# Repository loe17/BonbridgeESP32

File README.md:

# BonbridgeESP32

**Mach deinen USB-Bondrucker zum Netzwerk- und WLAN-Drucker für dein Kassensystem.**

Viele Kassensysteme (wie z. B. Kassensoftware, Gastronomiesoftware oder Kassen-Apps) können Bondrucker nur über das Netzwerk über eine **IP-Adresse und Port 9100** ansprechen. USB-Drucker können sie oft nicht direkt verwenden.

**BonbridgeESP32** löst dieses Problem mit einem kleinen, sparsamen Mikrocontroller (ESP32-S3):
Er nimmt Druckaufträge über ein **Netzwerkkabel (LAN)** oder über **WLAN** entgegen und leitet sie ohne Verzögerung direkt an deinen USB-Bondrucker weiter.

---

## Funktionen im Überblick

* **LAN & WLAN mit automatischer Umschaltung:**
  * **Kabel hat Vorrang:** Sobald ein Netzwerkkabel eingesteckt ist, nutzt der Adapter ausschließlich das Kabel. Das WLAN-Funkmodul wird komplett ausgeschaltet (spart Strom und schont das Funknetz).
  * **WLAN als Reserve:** Wird das Kabel abgezogen oder ist keins gesteckt, schaltet der Adapter automatisch das WLAN ein und verbindet sich mit deinem hinterlegten Funknetz.
* **Port 9100 RAW-Drucker-Server:** Der weltweite Standard für Netzwerk-Bondrucker. Druckdaten werden 1:1 an den USB-Drucker gestreamt.
* **1 Drucker pro Adapter:** Maximale Zuverlässigkeit – keine Vermischung von Bons.
* **Extrem sparsame Einstellungsseite (Web-Oberfläche):**
  * Im Browser erreichbar über die IP-Adresse des Geräts (`http://<ip>/`).
  * Verbraucht im Hintergrund **0 % Rechenleistung**, wenn sie nicht aufgerufen wird.
  * Zeigt sofort an, **worüber aktuell kommuniziert wird** (🟢 *LAN-Kabel aktiv* oder 🔵 *WLAN aktiv*).
  * Test-Knöpfe für **Drucktest** und **Kassenlade öffnen**.
  * Auswahl des **Druckprofils** (Epson TM-T88, Standard 80 mm, Kompakt 58 mm, Star).
  * Schalter: **Hinweis drucken wenn Netzwerk ausfällt**.
* **Bequeme WLAN-Suche & Live-Verbindung in der Web-Oberfläche:**
  * **🔍 WLAN suchen:** Findet alle Funknetze in Reichweite mit Signalstärke (z. B. 📶 85%) und Schlosssymbol. Ein Klick genügt, um das gewünschte WLAN auszuwählen.
  * **Passwort einblenden (👁️):** Zeigt das eingegebene Passwort im Klartext an, um Tippfehler sofort zu vermeiden.
  * **Direkt verbinden mit Live-Rückmeldung:** Ein Klick auf *„Mit diesem WLAN verbinden“* stellt die Verbindung her und zeigt nach wenigen Sekunden die neue IP-Adresse als anklickbaren Link an – oder bei Fehlern (z. B. Passwort falsch) eine verständliche Erklärung.
  * **Automatischer Einrichtungs-Hotspot (`Bonbridge-Setup`):** Ist noch kein WLAN hinterlegt oder der Router nicht erreichbar, spannt der Adapter ein eigenes Hilfsnetzwerk auf (`Bonbridge-Setup` unter `http://192.168.4.1`). So kann man das WLAN kinderleicht direkt vom Smartphone oder Laptop einrichten!
* **Drahtlose Firmware-Aktualisierung (Funk-Update / OTA) mit Versionsprüfung:**
  * **🔍 Automatische Versionsprüfung:** Ein Klick auf *„Nach Versionen auf GitHub suchen“* prüft, ob eine neuere Version bereitsteht oder man bereits aktuell ist.
  * **Auswahlmenü für Updates & Downgrades:** Zeigt alle jemals veröffentlichten Versionen an. Man kann mit einem Klick auf eine neuere Version aktualisieren oder bei Bedarf auf eine ältere Version zurückspringen (Downgrade).
  * **Manuelle Datei:** Ermöglicht das Hochladen einer eigenen `.bin`-Datei direkt über den Web-Browser.
  * **Live-Balken & Sicherheit:** Zeigt den Fortschritt von 0–100 % in Echtzeit an; alle gespeicherten WLAN- und Druckereinstellungen bleiben beim Update vollständig erhalten.
* **Netzwerk-Wächter (Ausfall-Alarm):**
  * Bricht die Netzwerkverbindung komplett ab, druckt der Drucker selbstständig einen Warnzettel aus:  
    *„Achtung: Netzwerkverbindung unterbrochen! Bitte LAN-Kabel oder Router prüfen.“*

---

## Benötigte Hardware

1. **Mikrocontroller:** **ESP32-S3** (z. B. ESP32-S3-DevKitC-1).  
   *(Wichtig: Ein älterer, klassischer ESP32 kann keine USB-Geräte als Host ansteuern – daher muss es ein ESP32-S3 sein!)*
2. **Netzwerk-Aufsatz:** **WIZnet W5500** SPI-Ethernet-Modul (für den LAN-Kabelanschluss).
3. **USB-OTG-Kabel / Buchse:** Zum Anstecken des Druckers an den ESP32-S3.
4. **Stromversorgung:** Über die Pins (5V und GND), z. B. von einem stabilen 5V-Netzteil oder dem 5V-Ausgang des Druckers.
5. **Bondrucker:** Beliebiger USB-ESC/POS-Bondrucker (z. B. Epson TM-T88V/VI, Munbyn, Bixolon, etc.).

---

## Verkabelung (Pin-Belegung)

### 1. Stromversorgung
| Netzteil / Quelle | ESP32-S3 Pin | Hinweise |
|---|---|---|
| **+5V (Plus)** | **5V** (bzw. VIN) | Stabiles 5V-Netzteil (mindestens **1,5 A bis 2 A** empfohlen) |
| **GND (Minus)** | **GND** | Gemeinsame Masse |

> [!TIP]
> **Tipps für eine stabile 5V-Stromversorgung:**
> * **5V über Pins oder USB:** Du kannst den ESP32-S3 über die Pins (**5V** und **GND**) mit einem 5V-Labornetzteil/Netzteil versorgen, oder direkt über ein 5V-USB-Netzteil (am besten mit Standard USB-A auf USB-C Kabel).
> * **Messpunkt zur Kontrolle:** Liegt an den Pins 5V an, muss am Pin **3V3** (gegen GND gemessen) eine saubere Spannung von 3,3 Volt anliegen.
> * Verwende möglichst **kurze und dicke Kabel** (keine langen, hauchdünnen Steckbrett-Drähte). Beim Senden von WLAN-Daten benötigt der Funkchip kurzzeitig Stromspitzen bis zu 450 mA – zu dünne Drähte führen zu einem Spannungsabfall (Brownout).
> * Das System verfügt über eine integrierte **Spannungsüberwachung**: Auf der Weboberfläche siehst du in der Zeile *„System-Start“* sofort, ob das Board sauber gestartet ist oder ob ein Spannungseinbruch aufgetreten ist.
> * Auch die 5V-Leitung der USB-Buchse für den Drucker muss mit 5V versorgt werden, damit der Druckeranschluss Strom hat.

### 2. W5500 Netzwerk-Modul (LAN-Kabel)

Das W5500-Modul wird über den SPI-Bus mit dem ESP32-S3 verbunden. Je nachdem, welches Entwicklungsboard du verwendest, wähle die passende Belegung:

#### 2.1 Für Seeed Studio XIAO ESP32-S3 (14-Pin Kompaktboard von Amazon)
Das daumengroße XIAO-Board führt nur 11 GPIO-Pins (GPIO 1–9, 43, 44) nach außen. Die Hardware-SPI-Pins sind dort auf **GPIO 7, 8 und 9** gelegt (im Hersteller-Pinout gelb als SCK, MISO, MOSI markiert):

| W5500 Pin | XIAO ESP32-S3 Pin | Board-Beschriftung | Funktion |
|---|---|---|---|
| **VCC** | **3.3V** | `3V3` (oben rechts) | **3,3V Stromversorgung** *(Achtung: Nicht an 5V!)* |
| **GND** | **GND** | `GND` (oben rechts) | Masse / Minus |
| **SCLK / CLK** | **GPIO 7** | `D8` / `SCK` (gelb) | SPI Taktleitung |
| **MISO** | **GPIO 8** | `D9` / `MISO` (gelb) | SPI Datenleitung vom W5500 zum ESP32 |
| **MOSI** | **GPIO 9** | `D10` / `MOSI` (gelb) | SPI Datenleitung vom ESP32 zum W5500 |
| **CS / SCS** | **GPIO 3** | `D2` (links) | Modulauswahl (Chip Select) |
| **INT** | **GPIO 2** | `D1` (links) | Unterbrechungssignal (Interrupt) |
| **RST** | **GPIO 1** | `D0` (links) | Hardware-Reset |

```text
       Seeed Studio XIAO ESP32-S3 (Draufsicht):
                 ┌─── USB-C ───┐
       (D0) GP1  │ [ ]     [ ] │ 5V
  RST ◄───── GP1 │             │ GND ──────► W5500 GND
  INT ◄───── GP2 │  ESP32-S3   │ 3V3 ──────► W5500 VCC (3.3V!)
   CS ◄───── GP3 │             │ GP9 ──────► W5500 MOSI (D10)
            GP4  │   [IPEX]    │ GP8 ──────► W5500 MISO (D9)
            GP5  │    Ant.     │ GP7 ──────► W5500 SCLK (D8)
            GP6  │             │ GP44 (D7)
       (D6) GP43 │             │ GP44
                 └─────────────┘
```

#### 2.2 Für großes ESP32-S3 DevKit (38/44 Pins) & Bonbridge Custom PCB
| W5500 Pin | ESP32-S3 Pin | Funktion |
|---|---|---|
| **VCC** | **3.3V** | Stromversorgung Modul (3,3V) |
| **GND** | **GND** | Masse / Minus |
| **MOSI** | **GPIO 11** | Datenleitung zum Modul |
| **MISO** | **GPIO 12** | Datenleitung vom Modul |
| **SCLK** | **GPIO 10** | Taktleitung |
| **CS / SCS** | **GPIO 9** | Modulauswahl (Chip Select) |
| **INT** | **GPIO 14** | Unterbrechungssignal |
| **RST** | **GPIO 13** | Rücksetzleitung (Reset) |

> [!NOTE]
> Die Pinbelegung kann in `config.h` über `#define BOARD_XIAO_ESP32S3` umgeschaltet werden. Standardmäßig ist das XIAO-Board bereits voreingestellt.

### 3. USB-Drucker-Anschluss (2 Optionen)

#### Option A: Standard-Anschluss per USB-OTG-Adapter (Extern)
* Am USB-C-Port des ESP32 wird ein einfacher **USB-OTG-Adapter (USB-C auf USB-A)** angeschlossen.
* Der Drucker wird mit seinem normalen Druckerkabel (USB-A auf USB-B) in den Adapter gesteckt.
* *Wichtig: Keinen USB-Hub verwenden!*

#### Option B: Direktverdrahtung & Festeinbau (Epson TM-T88 & diymore ESP32-S3)
Wer eine professionelle, kompakte Lösung ohne Adapter und ohne außen liegenden Kabelsalat möchte, kann das **diymore ESP32-S3 Entwicklungsboard** direkt mit den 4 Pins der USB-B-Buchse des Epson TM-T88 verbinden und das Board unsichtbar im Druckergehäuse integrieren.

##### Warum funktioniert das direkt an den Stiftleisten-Pins?
Der ESP32-S3 verfügt über einen internen USB-OTG-Controller, dessen Datenleitungen fest auf die GPIO-Pins herausgeführt sind:
* **GPIO 19** ist hardwaremäßig direkt mit **USB D-** verbunden.
* **GPIO 20** ist hardwaremäßig direkt mit **USB D+** verbunden.

##### Abbildung 1: Pinbelegung der USB-B-Buchse (Epson TM-T88)
Ansicht der USB-B-Buchse auf der Druckerplatine (von hinten / Lötseite):
```text
            ┌───────────────┐
            │   [2]   [1]   │     Pin 1 = VBUS (+5V)   --> Rote Ader
            │               │     Pin 2 = D- (Data -)  --> Weiße Ader
            │   [3]   [4]   │     Pin 3 = D+ (Data +)  --> Grüne Ader
            └───┬───────┬───┘     Pin 4 = GND (Masse)  --> Schwarze Ader
                │ Shield│
                └───────┘
```
> [!TIP]
> **Identifikation mit dem Multimeter:** Das metallene Abschirmgehäuse der USB-B-Buchse ist immer mit **GND** verbunden. Halte eine Prüfspitze an das Metallgehäuse und teste mit dem Durchgangsprüfer (Piepser) die 4 Pins: Nur **Pin 4** hat Durchgang zu GND. Damit weißt du sofort, wie die Buchse ausgerichtet ist!

##### Abbildung 2: Verdrahtungsschema zwischen Epson TM-T88 und Seeed Studio XIAO ESP32-S3
Auf der Rückseite des Seeed Studio XIAO ESP32-S3 befinden sich zwei dedizierte Lötpads **`D+`** und **`D-`**:

```text
Epson TM-T88 Platine (USB-B Buchse)              Seeed Studio XIAO ESP32-S3 (Rückseite)
┌─────────────────────────────────┐              ┌───────────────────────────┐
│ Pin 1: VBUS (+5V) ──────────────┼──[ Rot ]─────┼─► Pin 5V (VUSB)           │
│ Pin 2: D- (Data Minus) ─────────┼──[ Weiß ]────┼─► Lötpad D- (Unterseite)  │
│ Pin 3: D+ (Data Plus) ──────────┼──[ Grün ]────┼─► Lötpad D+ (Unterseite)  │
│ Pin 4: GND (Masse) ─────────────┼──[ Schwarz ]─┼─► Pin GND (Masse)         │
└─────────────────────────────────┘              └───────────────────────────┘
```

```text
               Seeed Studio XIAO ESP32-S3 (Rückseite):
                             ┌─── USB-C ───┐
                  (5V) VUSB  │             │ MTDI
                        GND  │   (Testpads)│ EN
                        3V3  │  D+      D- │ MTMS
                             │  [O]    [O] │ BAT -
                       (D10) │   ▲      ▲  │ BAT +
                        (D9) │   │      │  │
                        (D8) │   │      └───────► Weiß (D-) zum Drucker Pin 2
                        (D7) │   └──────────────► Grün (D+) zum Drucker Pin 3
                             │  [Thermal]  │
                             └─────────────┘
```

```mermaid
graph LR
    subgraph Epson ["Epson TM-T88 (USB-B Buchse)"]
        P1["Pin 1: VBUS (+5V)"]
        P2["Pin 2: D- (Data -)"]
        P3["Pin 3: D+ (Data +)"]
        P4["Pin 4: GND (Masse)"]
    end

    subgraph ESP ["diymore ESP32-S3"]
        V5["Pin 5V / VIN"]
        G19["Pin GPIO 19 (D-)"]
        G20["Pin GPIO 20 (D+)"]
        GND["Pin GND (Masse)"]
    end

    P1 -- "Rote Ader" --> V5
    P2 -- "Weiße Ader" --> G19
    P3 -- "Grüne Ader" --> G20
    P4 -- "Schwarze Ader" --> GND
```

##### Abbildung 3: All-in-One Festeinbau mit interner Stromversorgung (1 Netzteil für alles!)
Der Epson TM-T88 arbeitet intern mit einem 24V-Netzteil. Mit einem kleinen 24V-auf-5V-Abwärtswandler (Step-Down-Modul, z. B. MP1584EN oder LM2596 für ca. 1–2 €) kann der ESP32 direkt aus dem Drucker versorgt werden:

```text
                          ┌────────────────────────┐
   Epson 24V Netzteil ───►│ Epson TM-T88 Elektronik│
                          └──┬──────────────────┬──┘
                  +24V DC    │                  │  USB-B Pins (1, 2, 3, 4)
                  & GND      │                  │  (VBUS, D-, D+, GND)
                             ▼                  │
                   ┌──────────────────┐         │
                   │ Step-Down-Modul  │         │
                   │  (24V -> 5.0V)   │         │
                   └─────────┬────────┘         │
                      +5.0V  │                  │
                      & GND  ▼                  ▼
                   ┌───────────────────────────────┐
                   │    diymore ESP32-S3 Board     │
                   │ (Pins: 5V, GND, GPIO 19 & 20) │
                   └───────────────────────────────┘
```

> [!WARNING]
> **Achtung Spannung:** Der ESP32 verträgt am 5V-Pin maximal 5,0 bis 5,2 Volt. Verbinde niemals die 24V des Druckers direkt mit dem ESP32! Stelle den Step-Down-Wandler vor dem Anschließen mit einem Multimeter exakt auf 5,0V ein.

> [!NOTE]
> **Betrieb am Computer vs. Drucker-Betrieb:**
> * **Am Computer angeschlossen (USB-Kabel zum PC):** Der ESP32 erkennt die PC-Verbindung automatisch. Der USB-Druckermodus wird pausiert, damit der serielle Monitor und die Programmierung stabil funktionieren. Die Web-Oberfläche und das Netzwerk laufen uneingeschränkt.
> * **Im Kassen-/Drucker-Betrieb:** Betreibe das Board an einem 5V-Netzteil (z. B. 5V/GND-Pins oder interner Step-Down-Wandler). Der Drucker wird entweder über den USB-OTG-Adapter oder direkt über die Pins GPIO 19 & 20 angesteuert.

---

## Software auf den ESP32 übertragen

### Mit der Arduino IDE:
1. Starte die **Arduino IDE**.
2. Klicke im Menü auf **Datei -> Öffnen...** (oder drücke `Strg + O`).
3. Wähle im Ordner `BonbridgeESP32` die Datei **`BonbridgeESP32.ino`** aus.
4. Alle Programmteile öffnen sich nun automatisch als übersichtliche Reiter (Tabs).
5. Wähle unter **Werkzeuge -> Board -> esp32** dein Board aus: **ESP32S3 Dev Module**.
6. Stelle unter **Werkzeuge** folgende Werte ein:
   * **USB Mode:** *Hardware CDC and JTAG*
   * **USB CDC On Boot:** *Enabled* (Wichtig: Nur so sendet der Chip Text an den PC-Monitor!)
   * **PSRAM:** *Disabled* (Sehr wichtig: Verhindert Start-Absturzschleifen bei Super Mini Boards!)
   * **Flash Size:** *4MB* (oder *8MB*)
   * **Flash Mode:** *QIO 80MHz*
7. Verbinde den ESP32-S3 per USB-Kabel mit dem Computer, wähle den passenden **Port** aus und klicke auf den Pfeil (**Hochladen**).

### Mit PlatformIO (VS Code):
1. Projektordner `BonbridgeESP32` in VS Code öffnen.
2. Unten in der Leiste auf den Haken (**Build**) und dann auf den Pfeil (**Upload**) klicken.

---

## Erste Schritte & Bedienung

1. **Einschalten & Status-LED (Lebenszeichen & Farbcode):**
   * Direkt nach dem Einschalten leuchtet die RGB-LED (GPIO 48) **Violett** (bestätigt sofort: Stromversorgung steht, Prozessor läuft!).
   * **Grün (sanfter Puls / Herzschlag):** Erfolgreich mit dem Netzwerk (WLAN oder LAN) verbunden und betriebsbereit!
   * **Blau (Puls):** Einrichtungs-Hotspot (`Bonbridge-Setup`) ist aktiv – verbinde dich mit dem WLAN und öffne `http://192.168.4.1`.
   * **Gelb / Orange (blinkend):** Das Gerät sucht das WLAN und versucht die Verbindung zum Router herzustellen.
   * **LED bleibt dunkel?** Bitte mit einem Multimeter prüfen, ob zwischen Pin **3V3** und **GND** ca. 3,3 Volt anliegen (z. B. Kabelverbindung, Polung oder Strombegrenzung am Netzteil prüfen).
   * **Hinweis zur Lade-LED:** Auf manchen Boards befindet sich zusätzlich eine winzige rote Akkulade-LED. Diese erlischt nach wenigen Sekunden, weil kein Akku angeschlossen ist – das ist völlig normal!

2. **IP-Adresse sofort ablesen (Serieller Monitor):**
   * Öffne in der Arduino IDE oben rechts die Lupe (**Serieller Monitor**).
   * Stelle unten rechts die Geschwindigkeit auf **115200 Baud**.
   * Beim Starten oder Verbinden siehst du sofort im Klartext:
     * Die vergebene **IP-Adresse**
     * Ob **LAN-Kabel** oder **WLAN** aktiv ist
     * Die Web-Adresse (`http://...`) und den Drucker-Port (`:9100`)
     * Den Status deines angeschlossenen USB-Bondruckers

3. **Web-Oberfläche öffnen:**
   * **Über LAN-Kabel:** Stecke das Netzwerkkabel ein und öffne die im Seriellen Monitor angezeigte Adresse (z. B. `http://192.168.178.50`).
   * **Über den Einrichtungs-Hotspot:** Ist kein Kabel gesteckt und kein WLAN verbunden, verbinde dein Smartphone oder deinen Laptop mit dem WLAN **`Bonbridge-Setup`** (ohne Passwort) und öffne im Browser **`http://192.168.4.1`**.

4. **WLAN suchen & verbinden:**
   * Klicke neben dem Feld *WLAN Name* auf **`🔍 Suchen`**.
   * Nach ein bis zwei Sekunden erscheint eine Liste aller gefundenen Funknetze mit Empfangsstärke und Schlosssymbol.
   * Klicke dein Netzwerk in der Liste an – der Name wird automatisch ins Textfeld eingetragen.
   * Gib dein WLAN-Passwort ein (mit dem **`👁️`**-Symbol kannst du kontrollieren, ob alles richtig geschrieben ist).
   * Klicke auf **`Mit diesem WLAN verbinden`**:
     * Der Adapter stellt nun sofort die Verbindung her.
     * Nach wenigen Sekunden erhältst du direkt im Browser die Erfolgsmeldung mit der neuen IP-Adresse und einem anklickbaren Link!
     * Falls das Passwort falsch war oder der Empfang abbricht, wird dir der Grund sofort in verständlichem Deutsch angezeigt.
   * **Drucktest & Kassenlade:** Über die Schnell-Test-Knöpfe kannst du den Drucker und die Geldschublade direkt ausprobieren.

5. **Im Kassensystem einrichten:**
   * Wähle in deiner Kassen-App (z. B. Kassensoftware) **Netzwerk-Drucker / ESC-POS**.
   * Gib die vergebene **IP-Adresse** des BonbridgeESP32 ein.
   * Gib als Port **9100** ein.
   * Fertig! Ab sofort druckt deine Kasse zuverlässig über den Adapter.

6. **Firmware drahtlos aktualisieren & Downgrades durchführen (OTA):**
   * Rufe die Weboberfläche im Browser auf.
   * Scrolle nach unten zum Bereich **Firmware-Aktualisierung (Funk-Update / OTA)**.
   * **Versionen prüfen:** Klicke auf `🔍 Nach Versionen auf GitHub suchen`.
   * **Auswählen & Installieren:**
     * Es erscheint eine Liste aller freigegebenen Versionen aus dem GitHub-Projekt.
     * Wähle eine **neuere Version** aus, um das System zu aktualisieren.
     * Wähle eine **ältere Version** aus, falls du auf einen vorherigen Softwarestand zurückspringen möchtest (Downgrade).
     * Der Knopf passt sich automatisch an (z. B. `Auf v1.2.0 aktualisieren` oder `Auf v1.0.0 zurückstufen (Downgrade)`).
   * **Manuelle Datei:** Über `Datei auswählen` kannst du weiterhin jederzeit eine eigene `.bin`-Datei vom Computer hochladen.
   * Während der Übertragung siehst du einen Echtzeit-Ladebalken. Alle gespeicherten WLAN- und Druckeinstellungen bleiben vollständig erhalten.

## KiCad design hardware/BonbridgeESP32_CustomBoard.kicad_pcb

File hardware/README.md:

# BonbridgeESP32 - Eigene Hardware-Entwicklung (KiCad)

Vollständige Anleitung und Projektdaten für eine maßgeschneiderte All-in-One-Platine für den Festeinbau in den **Epson TM-T88 Bondrucker**.

---

## 1. Spezifikationen & Mechanik

* **Abmessungen:** Exakt **55,0 mm × 25,0 mm** (mit abgerundeten Ecken  = 2,0\text{ mm}$).
* **Befestigung:** 4× M2,5-Montagebohrungen (Bohrung 2,7 mm, Kupfer-Pad 3,8 mm, mit Masse/GND verbunden).
* **Ausrichtung & Platzierung der Anschlüsse:**
  * **Untere Längsseite (55 mm Kante):**
    * **RJ45 MagJack (J1):** Netzwerkbuchse (10/100Mbit mit Übertragern & LEDs). **Ragt 3,0 mm über den unteren Rand der Platine hinaus** (Vorderkante bei  = 128,0\text{ mm}$), damit die Buchse bündig durch einen Gehäuseausschnitt geführt werden kann.
  * **Obere Längsseite (55 mm Kante):**
    * **JST-XH 2-Pin (J3, oben links):** 24V Stromeingang vom internen Druckernetzteil (+24V, GND).
    * **JST-XH 4-Pin (J4, direkt neben J3):** 4-Pin USB-Verbindung zum Drucker-Mainboard (+5V, D-, D+, GND).
    * **USB-C Buchse (J2, gegenüber RJ45):** Zum Programmieren/Flashen und Diagnose (öffnet nach oben).
* **Externe Antenne:** Anschluss über integrierte **U.FL / IPEX Buchse** direkt auf dem ESP32-S3-WROOM-1U Modul (liegt frei zugänglich an der rechten Platinenkante).
* **DRC-Status:** **0 Fehler, 0 Warnungen** im KiCad 10 Design Rule Check!

---

## 2. Platinen-Vorschau (3D-Render & Layout)

*Draufsicht (Top-Layer F.Cu) des fertig bestückten Platinen-Layouts (55 × 25 mm)*

*3D-Isometrie-Ansicht mit 3 mm Überhang der RJ45-Buchse nach unten*

*Rückseite (Bottom-Layer B.Cu) mit EMV-optimierter Entkoppelung und Ethernet-Terminierung*

`	ext
       ┌─── 55 mm Längsseite (Oben) ──────────────────────────────────────┐
       │ (H1)  [J3] 24V    [J4] PRINTER USB     [J2] PROG  ┌───────────┐  │
       │ M2.5  [+24V G]    [+5V D- D+ GND]      USB-C      │           │  │
       │                                        [U4] 3.3V  │           │  │
       │ ┌────────────────┐                     ┌───────┐  │ ESP32-S3  │  │ (H2)
       │ │                │                     │ W5500 │  │ WROOM-1U  │  │ M2.5
       │ │  RJ45 MagJack  │                     │ QFN48 │  │           │  │
       │ │  (10/100Mbit)  │                     └───────┘  │   [IPEX]  │ [D1]
       │ │                │                     [U3]Buck   │   Ant.    │ RGB
       │ └────────────────┘                     [L1]4.7uH  └───────────┘  │
       │ (H3)                                                        (H4) │
       │ M2.5                                                        M2.5 │
       └───┬────────────┬─────────────────────────────────────────────────┘
           │  RJ45 3mm  │ ◄─── Ragt 3,0 mm über den Rand (für Gehäuseausschnitt)
           └────────────┘
`

---

## 3. Bauteilauswahl & Vollständige Stückliste (BOM)

| Ref | Komponente / Wert | Gehäuse | Ebene | Funktion & Begründung |
|---|---|---|---|---|
| **U1** | **ESP32-S3-WROOM-1U-N16R8** | SMD (18×19,2 mm) | F.Cu | **Mit U.FL/IPEX-Buchse für externe Antenne.** Spart 6 mm Baulänge gegenüber der PCB-Antennen-Version! |
| **U2** | **WIZnet W5500** | QFN-48 (7×7 mm) | F.Cu | Hardware-TCP/IP-Chip. Wird über SPI mit dem ESP32 verbunden. |
| **J1** | **RJ45 MagJack (10/100M)** | THT | F.Cu | Buchse mit integrierten Übertragern & LEDs (Amphenol RJMG1BD3B8K1ANR). **Ragt 3 mm über Rand.** |
| **J2** | **USB-C Receptacle** | SMD (TYPE-C-31-M-12) | F.Cu | Auf oberer Längsseite gegenüber RJ45. Zum Programmieren und Flashen. |
| **J3** | **JST-XH 2-Pin (2,50 mm)** | THT vertikal | F.Cu | 24V-Stromeingang vom internen Druckernetzteil (+24V, GND). |
| **J4** | **JST-XH 4-Pin (2,50 mm)** | THT vertikal | F.Cu | 4-Pin USB-Verbindung direkt zum Drucker-Mainboard (+5V, D-, D+, GND). |
| **U3** | **TI TPS54302** | SOT-23-6 | F.Cu | Abwärtsregler (Buck): Wandelt 24V DC hocheffizient auf 5,0V (bis 3A) für Drucker-USB und 3.3V-LDO. |
| **L1** | **4,7 µH (Bourns SRN4018)** | SMD (4×4 mm) | F.Cu | Speicherdrossel für den TPS54302 Step-Down-Wandler. |
| **U4** | **Diodes AP2112K-3.3** | SOT-23-5 | F.Cu | Ultra-Low-Noise LDO: Erzeugt saubere 3,3V (bis 600 mA) für ESP32-S3 und W5500. |
| **D1** | **WS2812B RGB Status-LED** | SMD PLCC4 | F.Cu | Adressierbare Smart-RGB-LED an GPIO 48 an der rechten Außenkante. |
| **SW1**| **Reset-Taster (SKRK)** | SMD 3×4 mm | F.Cu | Manueller EN/Reset-Taster (obere Kante). |
| **SW2**| **Boot-Taster (SKRK)** | SMD 3×4 mm | F.Cu | GPIO 0 Boot-Modus-Taster (untere Kante). |
| **C1** | **10 µF / 50V** | 1206 SMD | F.Cu | 24V Eingangs-Glättungskondensator. |
| **C2** | **100 nF / 50V** | 0603 SMD | F.Cu | 24V Hochfrequenz-Filter. |
| **C3** | **100 nF** | 0603 SMD | F.Cu | Bootstrap-Kondensator für TPS54302 (Pins BOOT zu SW). |
| **C4, C5** | **22 µF / 10V (2×)** | 0805 SMD | B.Cu | 5V Ausgangs-Glättungskondensatoren (direkt unter Induktivität L1). |
| **R1** | **100 kΩ (1%)** | 0603 SMD | B.Cu | Feedback-Spannungsteiler R_top für 5,0V Ausgang. |
| **R2** | **13,3 kΩ (1%)** | 0603 SMD | B.Cu | Feedback-Spannungsteiler R_bottom für 5,0V Ausgang. |
| **C6** | **4,7 µF** | 0603 SMD | F.Cu | LDO Eingangs-Kondensator (+5V). |
| **C7** | **4,7 µF** | 0603 SMD | F.Cu | LDO Ausgangs-Kondensator (+3,3V). |
| **R11, R12** | **5,1 kΩ (2×)** | 0603 SMD | B.Cu | USB-C CC1 / CC2 Pull-Down Widerstände für 5V-Aushandlung. |
| **R3** | **12,4 kΩ (1%)** | 0603 SMD | B.Cu | W5500 PHY BIAS-Referenzwiderstand nach GND. |
| **R4** | **10 kΩ** | 0603 SMD | B.Cu | W5500 Reset Pull-Up Widerstand nach +3,3V. |
| **C10, C11**| **100 nF (2×)** | 0603 SMD | B.Cu | W5500 Entkopplungskondensatoren (direkt an Versorgungs-Vias). |
| **R5, R6** | **49,9 Ω (1%) (2×)** | 0603 SMD | B.Cu | RJ45 Ethernet TX+ / TX- Leitungsabschluss. |
| **R7, R8** | **49,9 Ω (1%) (2×)** | 0603 SMD | B.Cu | RJ45 Ethernet RX+ / RX- Leitungsabschluss. |
| **C14**| **10 nF / 2 kV** | 0805 SMD | B.Cu | Bob-Smith Hochspannungs-Abschlusskondensator für LAN-Übertrager. |
| **C15**| **10 µF** | 0805 SMD | F.Cu | ESP32-S3 3,3V Bulk-Pufferkondensator. |
| **C16**| **100 nF** | 0603 SMD | F.Cu | ESP32-S3 Hochfrequenz-Entkopplung. |
| **R13**| **10 kΩ** | 0603 SMD | B.Cu | ESP32-S3 EN (Reset) Pull-Up nach +3,3V. |
| **C17**| **1 µF** | 0603 SMD | B.Cu | ESP32-S3 EN RC-Verzögerungsglied für zuverlässigen Power-On Reset. |
| **C18**| **100 nF** | 0603 SMD | F.Cu | WS2812B RGB-LED Pufferkondensator. |

---

## 4. Verdrahtungs- & Pinbelegung

### 4.1 ESP32-S3 zu W5500 (SPI-Schnittstelle)
* GPIO 10 ➔ W5500 SCLK (Takt)
* GPIO 11 ➔ W5500 MOSI (Daten zum Chip)
* GPIO 12 ➔ W5500 MISO (Daten vom Chip)
* GPIO 9  ➔ W5500 CS (Chip Select)
* GPIO 14 ➔ W5500 INT (Interrupt)
* GPIO 13 ➔ W5500 RST (Hardware-Reset)

### 4.2 ESP32-S3 zum Drucker-Mainboard (JST-XH 4-Pin - J4)
* Pin 1 ➔ +5,0V (Ausgang vom Step-Down-Wandler)
* Pin 2 ➔ GPIO 19 (USB D-)
* Pin 3 ➔ GPIO 20 (USB D+)
* Pin 4 ➔ GND (Gemeinsame Masse)

### 4.3 USB-C Programmierbuchse (J2)
* A6 / B6 (D+) ➔ GPIO 20
* A7 / B7 (D-) ➔ GPIO 19
* CC1 ➔ 5,1 kΩ Widerstand nach GND
* CC2 ➔ 5,1 kΩ Widerstand nach GND
* VBUS ➔ Anode von Schottky-Diode D2 ➔ Kathode an +5V-Schiene

### 4.4 Status-LED
* GPIO 48 ➔ DIN der WS2812B RGB-LED

---

## 5. Das KiCad-Projekt verwenden

Die Projektdateien befinden sich direkt in diesem Ordner:
* **BonbridgeESP32_CustomBoard.kicad_pro**: KiCad Projektdatei mit konfigurierten Fertigungsregeln.
* **BonbridgeESP32_CustomBoard.kicad_pcb**: Vollständig bestücktes und DRC-verifiziertes Board-Layout (55×25 mm, 0 Fehler). Getestet und nativ kompatibel mit KiCad 10.0!
* **generate_kicad_project.py**: Python-Generatorskript, das das gesamte Board inklusive aller Bauteile, Netzlisten und Geometrien automatisiert generiert.
* **drc_report.txt**: Offizieller DRC-Prüfbericht (0 Fehler / 0 Warnungen).

### Lagenaufbau (Stackup-Empfehlung):
* **4-Lagen-Platine (1,6 mm Dicke, z. B. JLCPCB JLC04161H-7628):**
  * *Lage 1 (F.Cu - Top):* Signale & Hauptkomponenten (ESP32, W5500, Buchsen, Induktivität)
  * *Lage 2 (In1.Cu):* Durchgehende GND-Massefläche für minimale Störstrahlung und optimalen Rückstrom
  * *Lage 3 (In2.Cu):* Power-Planes für +5,0V und +3,3V
  * *Lage 4 (B.Cu - Bottom):* Entkopplungskondensatoren, Terminierungswiderstände & Masse

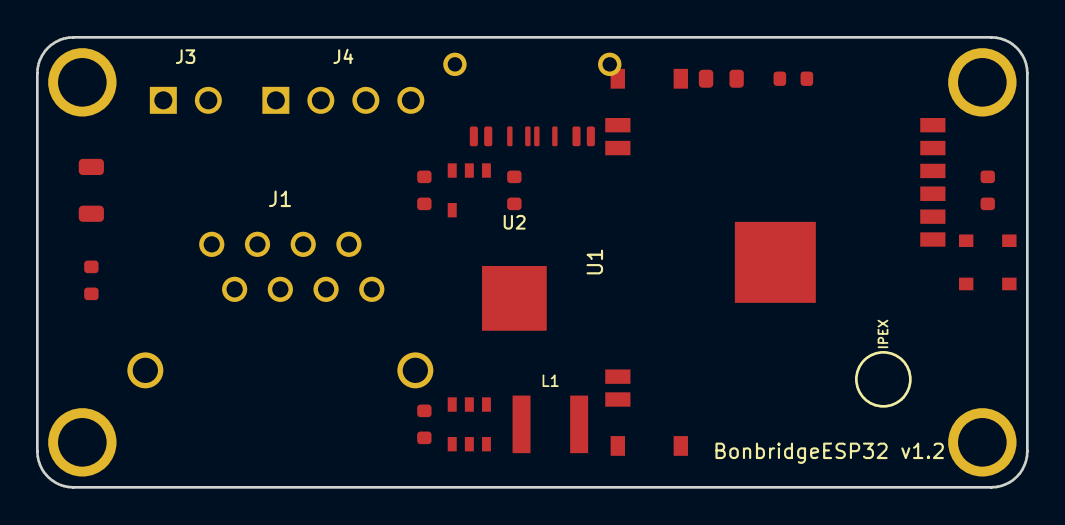
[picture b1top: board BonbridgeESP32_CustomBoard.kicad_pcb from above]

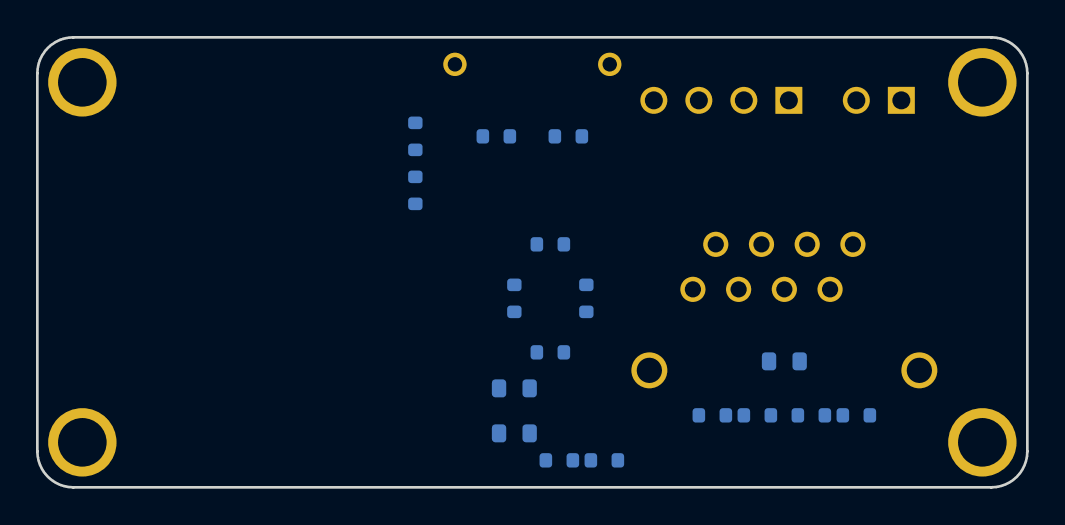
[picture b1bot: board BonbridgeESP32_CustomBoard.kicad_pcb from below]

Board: 2 copper layers, 55.0 x 25.0 mm, 41 parts (17 on the bottom side), 6 nets, no tracks yet.

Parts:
C1: 10uF/50V; C_1206_3216Metric
C2, C10, C11, C16, C18: 100nF; R_0603_1608Metric
C3: 100nF_BOOT; R_0603_1608Metric
C4, C5: 22uF_5V; C_0805_2012Metric
C6: 4.7uF_IN; R_0603_1608Metric
C7: 4.7uF_OUT; R_0603_1608Metric
C14: 10nF/2kV; C_0805_2012Metric
C15: 10uF; C_0805_2012Metric
C17: 1uF_EN; R_0603_1608Metric
D1: RGB; LED_WS2812B_PLCC4_5.0x5.0mm_P3.2mm
H1, H2, H3, H4: M2.5; MountingHole_2.7mm_M2.5_Pad_TopBottom
J1: RJ45 (+3mm); RJ45_Amphenol_RJMG1BD3B8K1ANR
J2: USB-C; USB_C_Receptacle_HRO_TYPE-C-31-M-12
J3: 24V_IN; JST_XH_B2B-XH-A_1x02_P2.50mm_Vertical
J4: PRINTER_USB; JST_XH_B4B-XH-A_1x04_P2.50mm_Vertical
L1: 4.7uH; L_Bourns-SRN4018
R1: 100k_FB; R_0603_1608Metric
R2: 13.3k_FB; R_0603_1608Metric
R3: 12.4k_BIAS; R_0603_1608Metric
R4: 10k_RST; R_0603_1608Metric
R5, R6, R7, R8: 49.9R; R_0603_1608Metric
R11: 5.1k_CC1; R_0603_1608Metric
R12: 5.1k_CC2; R_0603_1608Metric
R13: 10k_EN; R_0603_1608Metric
SW1: RESET; SW_Push_SPST_NO_Alps_SKRK
SW2: BOOT; SW_Push_SPST_NO_Alps_SKRK
U1: ESP32-S3-WROOM-1U
U2: W5500; QFN-48-1EP_7x7mm_P0.5mm_EP5.15x5.15mm
U3: Buck; SOT-23-6
U4: 3.3V; SOT-23-5

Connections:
+3V3: D1.1, U1.2, U4.5
+5V: J2.A4, J2.B9, J4.1, L1.2, U4.1, U4.3
+24V: J3.1, U3.5
GND: D1.3, J1.SH1, J1.SH2, J2.A1, J2.B12, J2.SH1, J2.SH2, J3.2, J4.4, SW1.1, SW2.1, U1.1, U1.EP, U2.EP, U3.2, U4.2
USB_DM: J2.A7, J4.2, U1.13
USB_DP: J2.A6, J4.3, U1.14
